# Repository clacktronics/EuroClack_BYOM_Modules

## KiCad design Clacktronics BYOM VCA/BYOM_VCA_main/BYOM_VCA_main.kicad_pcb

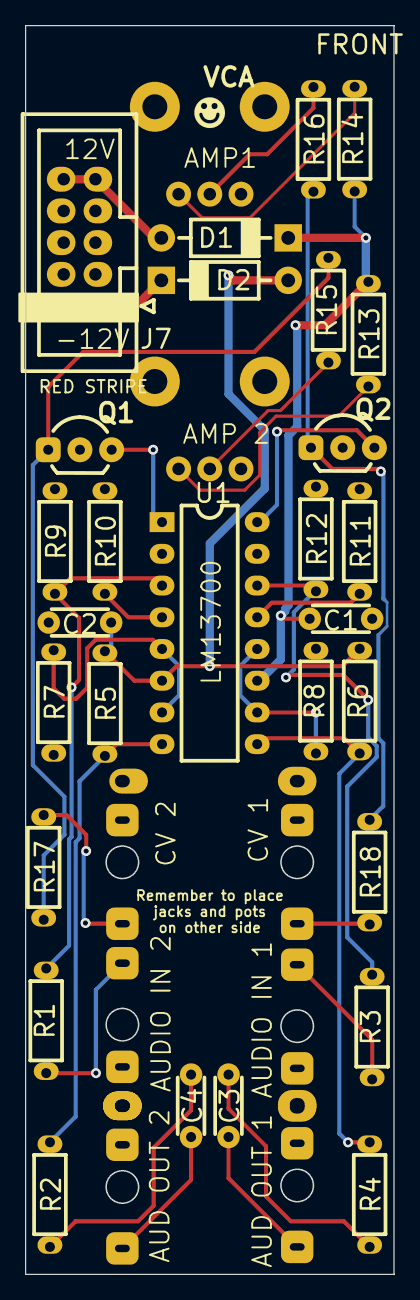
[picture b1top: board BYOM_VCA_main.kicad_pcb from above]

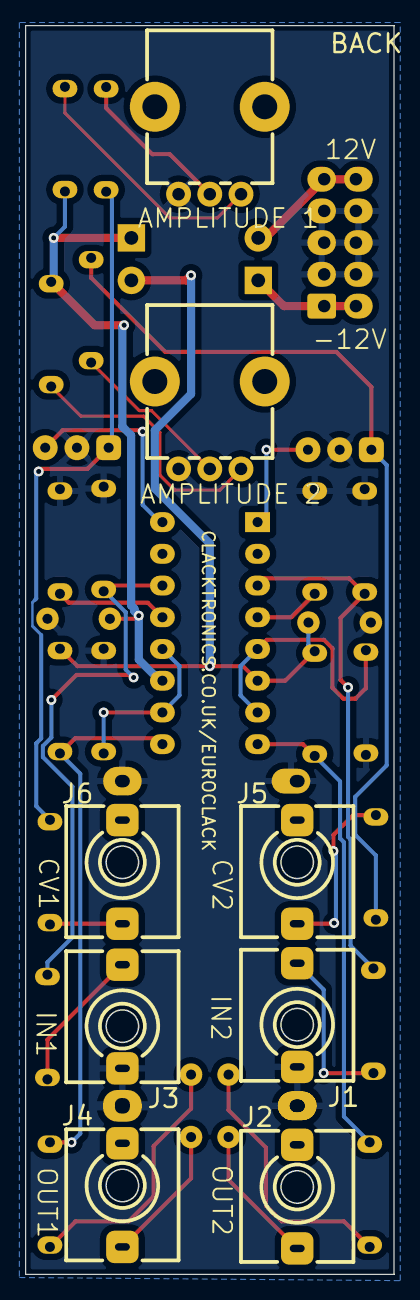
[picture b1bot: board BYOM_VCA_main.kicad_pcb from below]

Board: 2 copper layers, 29.5 x 100.0 mm, 36 parts (8 on the bottom side), 29 nets.

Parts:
C1, C2, C3, C4: 100n; C_TH_Disc_P5.00mm
D1, D2: 1N5817; D_TH_DO-41_P10.16mm
J1: AUDIO IN 2; Jack_3.5mm_QingPu_WQP-PJ398SM_Vertical
J2: AUDIO_OUT_2; Jack_3.5mm_QingPu_WQP-PJ398SM_Vertical
J3: AUDIO IN 1; Jack_3.5mm_QingPu_WQP-PJ398SM_Vertical
J4: AUDIO_OUT_1; Jack_3.5mm_QingPu_WQP-PJ398SM_Vertical
J5: CV 2; Jack_3.5mm_QingPu_WQP-PJ398SM_Vertical
J6: CV 1; Jack_3.5mm_QingPu_WQP-PJ398SM_Vertical
J7: Eurorack socket; IDC-Header_2x05_P2.54mm_Vertical
Q1, Q2: 2N3906; TO-92_Inline_Wide
R1, R3, R16: 100k; R_Axial_DIN0204_L3.6mm_D1.6mm_P7.62mm_Horizontal
R2, R4, R9, R10, R11, R12: 1k; R_Axial_DIN0204_L3.6mm_D1.6mm_P7.62mm_Horizontal
R5, R6, R7, R8: 22k; R_Axial_DIN0204_L3.6mm_D1.6mm_P7.62mm_Horizontal
R13, R14, R15, R17, R18: 10k; R_Axial_DIN0204_L3.6mm_D1.6mm_P7.62mm_Horizontal
RV1, RV2: 100k; POT_TH_Alps_RK09K_Single_Vertical
U1: LM13700; DIP-16_W7.62mm_LongPads

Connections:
+12V: C1.1, D1.1 (K), R13.2, R14.2, U1.11 (V+)
-12V: C2.2, D2.2 (A), R5.1, R6.1, U1.6 (V-)
GND: C1.2, C2.1, J1.S, J1.TN, J2.S, J3.S, J3.TN, J4.S, J5.S, J6.S, J7.3, J7.4, J7.5, J7.6, J7.7, J7.8, Q1.2 (B), Q2.2 (B), R7.1, R8.1, R9.2, R10.2, R11.2, R12.2, RV1.3, RV2.3
unnamed: C3.1, R4.1
unnamed: C3.2, J4.T
unnamed: C4.1, R2.1
unnamed: C4.2, J2.T
unnamed: D1.2 (A), J7.9, J7.10
unnamed: D2.1 (K), J7.1, J7.2
unnamed: J1.T, R1.2
unnamed: J3.T, R3.2
unnamed: J5.T, R17.2
unnamed: J6.T, R18.2
unnamed: Q1.3 (C), U1.1
unnamed: Q1.1 (E), R15.1, R17.1
unnamed: Q2.3 (C), U1.16
unnamed: Q2.1 (E), R16.1, R18.1
unnamed: R2.2, R5.2, U1.8
unnamed: R4.2, R6.2, U1.9
unnamed: R7.2, U1.5, U1.7
unnamed: R8.2, U1.10, U1.12
unnamed: R13.1, RV1.1
unnamed: R14.1, RV2.1
unnamed: R15.2, RV1.2
unnamed: R16.2, RV2.2
unnamed: R3.1, R12.1, U1.14 (+)
unnamed: R11.1, U1.13 (-)
unnamed: R1.1, R9.1, U1.3 (+)
unnamed: R10.1, U1.4 (-)

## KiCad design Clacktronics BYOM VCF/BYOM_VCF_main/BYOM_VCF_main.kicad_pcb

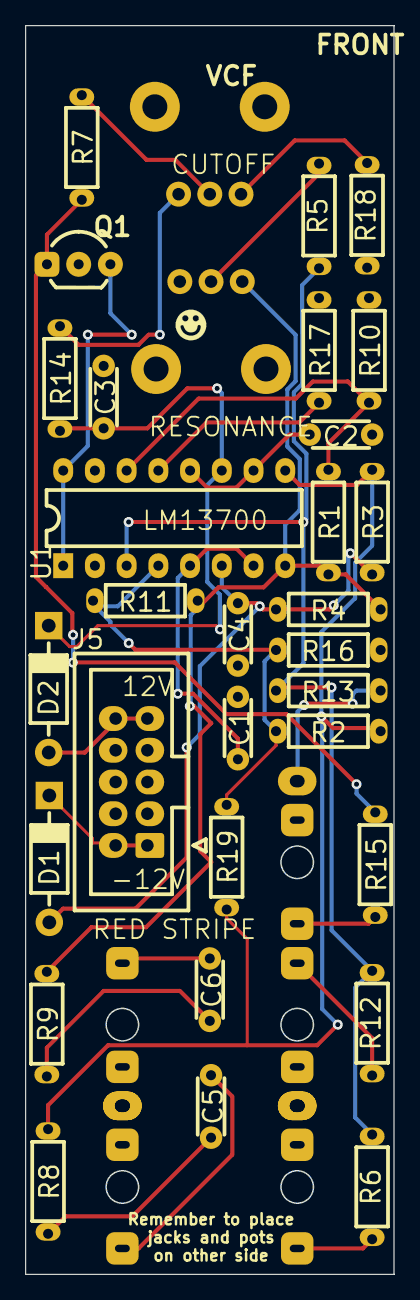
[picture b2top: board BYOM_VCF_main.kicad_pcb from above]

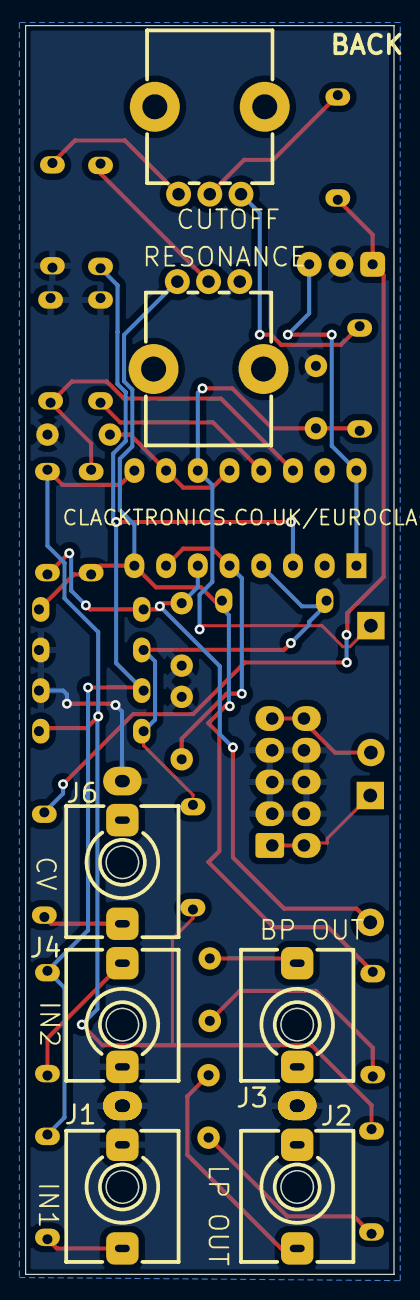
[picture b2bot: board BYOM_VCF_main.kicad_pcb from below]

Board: 2 copper layers, 29.5 x 100.0 mm, 37 parts (7 on the bottom side), 26 nets.

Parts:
C1, C2: 470pF; C_TH_Disc_P5.00mm
C3, C4, C5, C6: 100n; C_TH_Disc_P5.00mm
D1, D2: 1N5817; D_TH_DO-41_P10.16mm
J1: AUDIO IN 2; Jack_3.5mm_QingPu_WQP-PJ398SM_Vertical
J2: LP OUT; Jack_3.5mm_QingPu_WQP-PJ398SM_Vertical
J3: BP OUT; Jack_3.5mm_QingPu_WQP-PJ398SM_Vertical
J4: AUDIO IN 1; Jack_3.5mm_QingPu_WQP-PJ398SM_Vertical
J5: Eurorack socket; IDC-Header_2x05_P2.54mm_Vertical
J6: CUTOFF CV; Jack_3.5mm_QingPu_WQP-PJ398SM_Vertical
Q1: 2N3906; TO-92_Inline_Wide
R1, R3, R4, R5, R11: 22k; R_Axial_DIN0204_L3.6mm_D1.6mm_P7.62mm_Horizontal
R2, R6, R12, R14, R19: 100k; R_Axial_DIN0204_L3.6mm_D1.6mm_P7.62mm_Horizontal
R7, R15, R18: 10k; R_Axial_DIN0204_L3.6mm_D1.6mm_P7.62mm_Horizontal
R8, R9, R10, R13, R16, R17: 1k; R_Axial_DIN0204_L3.6mm_D1.6mm_P7.62mm_Horizontal
RV1, RV2: 100k; POT_TH_Alps_RK09K_Single_Vertical
U1: LM13700; DIP-16_W7.62mm_LongPads

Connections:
+12V: C3.1, D2.1 (K), R14.1, U1.11 (V+)
-12V: C4.2, D1.2 (A), R3.1, R4.1, U1.6 (V-)
GND: C1.2, C2.2, C3.2, C4.1, J1.S, J1.TN, J2.S, J3.S, J4.S, J4.TN, J5.3, J5.4, J5.5, J5.6, J5.7, J5.8, J6.S, Q1.2 (B), R10.2, R13.2, R16.2, R17.2, R18.2, RV1.3
unnamed: C1.1, U1.5, U1.7
unnamed: C2.1, U1.10, U1.12
unnamed: C5.1, R8.1
unnamed: C5.2, J2.T
unnamed: C6.1, R9.1
unnamed: C6.2, J3.T
unnamed: D1.1 (K), J5.1, J5.2
unnamed: D2.2 (A), J5.9, J5.10
unnamed: J1.T, R6.2
unnamed: J4.T, R12.2
unnamed: J6.T, R15.1
unnamed: Q1.3 (C), U1.1, U1.16
unnamed: Q1.1 (E), R7.1, R15.2
unnamed: R1.1, R4.2, R9.2, R11.2, RV1.1, U1.8
unnamed: R5.1, RV1.2
unnamed: R7.2, RV2.2
unnamed: R14.2, RV2.1
unnamed: R18.1, RV2.3
unnamed: R2.2, R3.2, R8.2, R19.2, U1.9
unnamed: R1.2, R10.1, U1.14 (+)
unnamed: R17.1, U1.13 (-)
unnamed: R5.2, R6.1, R12.1, R13.1, U1.3 (+)
unnamed: R2.1, R11.1, R16.1, R19.1, U1.4 (-)

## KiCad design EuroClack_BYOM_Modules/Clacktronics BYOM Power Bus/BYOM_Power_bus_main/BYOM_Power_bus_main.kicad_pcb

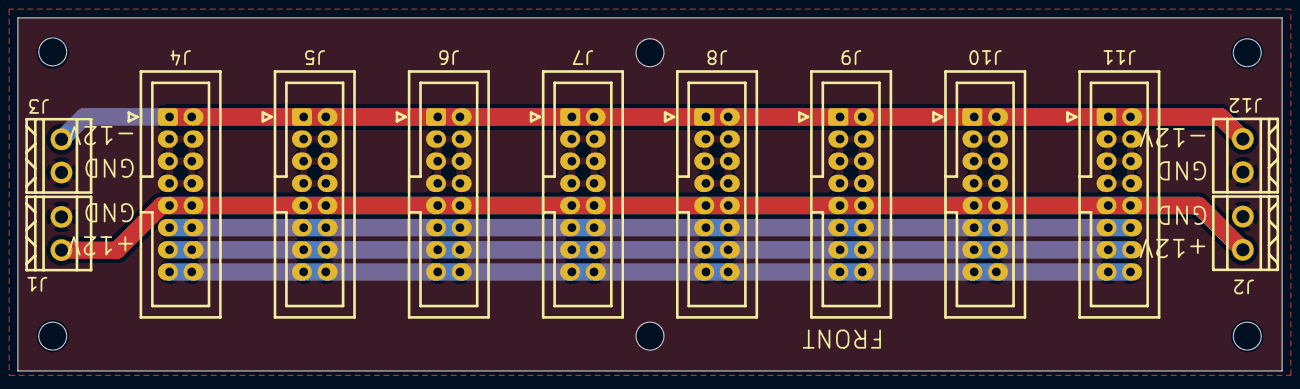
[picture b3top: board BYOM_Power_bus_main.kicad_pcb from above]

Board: 2 copper layers, 145.0 x 40.5 mm, 12 parts (0 on the bottom side), 6 nets.

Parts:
J1, J2, J3, J12: Screw_Terminal_01x02; 5.08 01X02
J4, J5, J6, J7, J8, J9, J10, J11: EURORACK_16_PIN; IDC-Header_2x08_P2.54mm_Vertical

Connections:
+12V: J1.2, J2.1, J4.9, J4.10, J5.9, J5.10, J6.9, J6.10, J7.9, J7.10, J8.9, J8.10, J9.9, J9.10, J10.9, J10.10, J11.9, J11.10
-12V: J3.1, J4.1, J4.2, J5.1, J5.2, J6.1, J6.2, J7.1, J7.2, J8.1, J8.2, J9.1, J9.2, J10.1, J10.2, J11.1, J11.2, J12.2
GND: J1.1, J2.2, J3.2, J4.3, J4.4, J4.5, J4.6, J4.7, J4.8, J5.3, J5.4, J5.5, J5.6, J5.7, J5.8, J6.3, J6.4, J6.5, J6.6, J6.7, J6.8, J7.3, J7.4, J7.5, J7.6, J7.7, J7.8, J8.3, J8.4, J8.5, J8.6, J8.7, J8.8, J9.3, J9.4, J9.5, J9.6, J9.7, J9.8, J10.3, J10.4, J10.5, J10.6, J10.7, J10.8, J11.3, J11.4, J11.5, J11.6, J11.7, J11.8, J12.1
unnamed: J4.11, J4.12, J5.11, J5.12, J6.11, J6.12, J7.11, J7.12, J8.11, J8.12, J9.11, J9.12, J10.11, J10.12, J11.11, J11.12
unnamed: J4.13, J4.14, J5.13, J5.14, J6.13, J6.14, J7.13, J7.14, J8.13, J8.14, J9.13, J9.14, J10.13, J10.14, J11.13, J11.14
unnamed: J4.15, J4.16, J5.15, J5.16, J6.15, J6.16, J7.15, J7.16, J8.15, J8.16, J9.15, J9.16, J10.15, J10.16, J11.15, J11.16
